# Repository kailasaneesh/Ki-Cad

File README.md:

# 4-Bit Binary Counter using D Flip-Flops

## Overview

This folder contains a 4-bit binary counter designed using KiCad. The circuit is implemented using 74LS74 D Flip-Flops and demonstrates the operation of a binary counter using sequential logic.

## Software Used

- KiCad

## Circuit Description

The design consists of cascaded 74LS74 D Flip-Flops driven by a pulse clock source to generate a 4-bit binary counting sequence.

The schematic and PCB layout were created using KiCad.

## Learning Outcome

- Understanding binary counter operation
- Understanding D Flip-Flop based sequential circuits
- Learning schematic capture using KiCad
- Learning basic PCB layout design
-

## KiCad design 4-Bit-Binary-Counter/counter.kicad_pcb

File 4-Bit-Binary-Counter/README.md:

# 4-Bit Binary Counter using D Flip-Flops

## Overview

This folder contains a 4-bit binary counter designed using KiCad. The circuit is implemented using 74LS74 D Flip-Flops and demonstrates the operation of a binary counter using sequential logic.

## Software Used

- KiCad

## Circuit Description

The design consists of cascaded 74LS74 D Flip-Flops driven by a pulse clock source to generate a 4-bit binary counting sequence.

The schematic and PCB layout were created using KiCad.

## Learning Outcome

- Understanding binary counter operation
- Understanding D Flip-Flop based sequential circuits
- Learning schematic capture using KiCad
- Learning basic PCB layout design

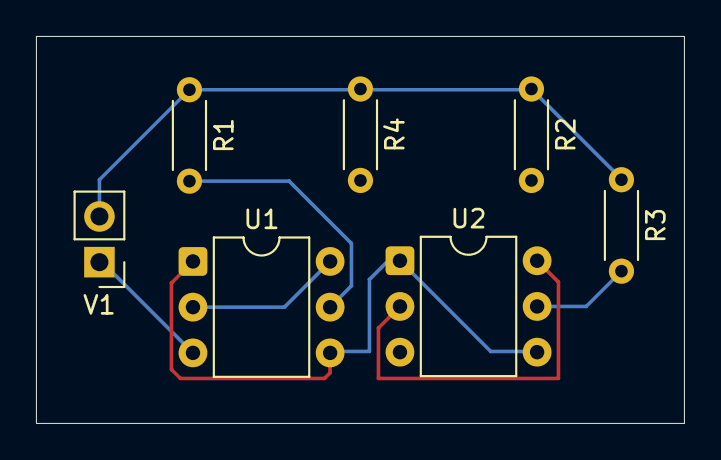
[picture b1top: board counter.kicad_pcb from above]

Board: 2 copper layers, 36.0 x 21.5 mm, 7 parts (0 on the bottom side), 7 nets.

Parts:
R1, R2, R3, R4: 330; R_Axial_DIN0204_L3.6mm_D1.6mm_P5.08mm_Horizontal
U1, U2: 74LS74; DIP-6_W7.62mm
V1: VPULSE; PinHeader_1x02_P2.54mm_Vertical

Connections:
+5V: U1.1 (~R), U1.4 (~S), U2.1 (~R), U2.4 (~S)
GND: R1.1, R2.1, R3.1, R4.1, V1.2
IN: U1.3 (C), V1.1
unnamed: U1.2 (D), U1.6 (~Q)
unnamed: R1.2, U1.5 (Q)
unnamed: U2.2 (D), U2.6 (~Q)
unnamed: R3.2, U2.5 (Q)
